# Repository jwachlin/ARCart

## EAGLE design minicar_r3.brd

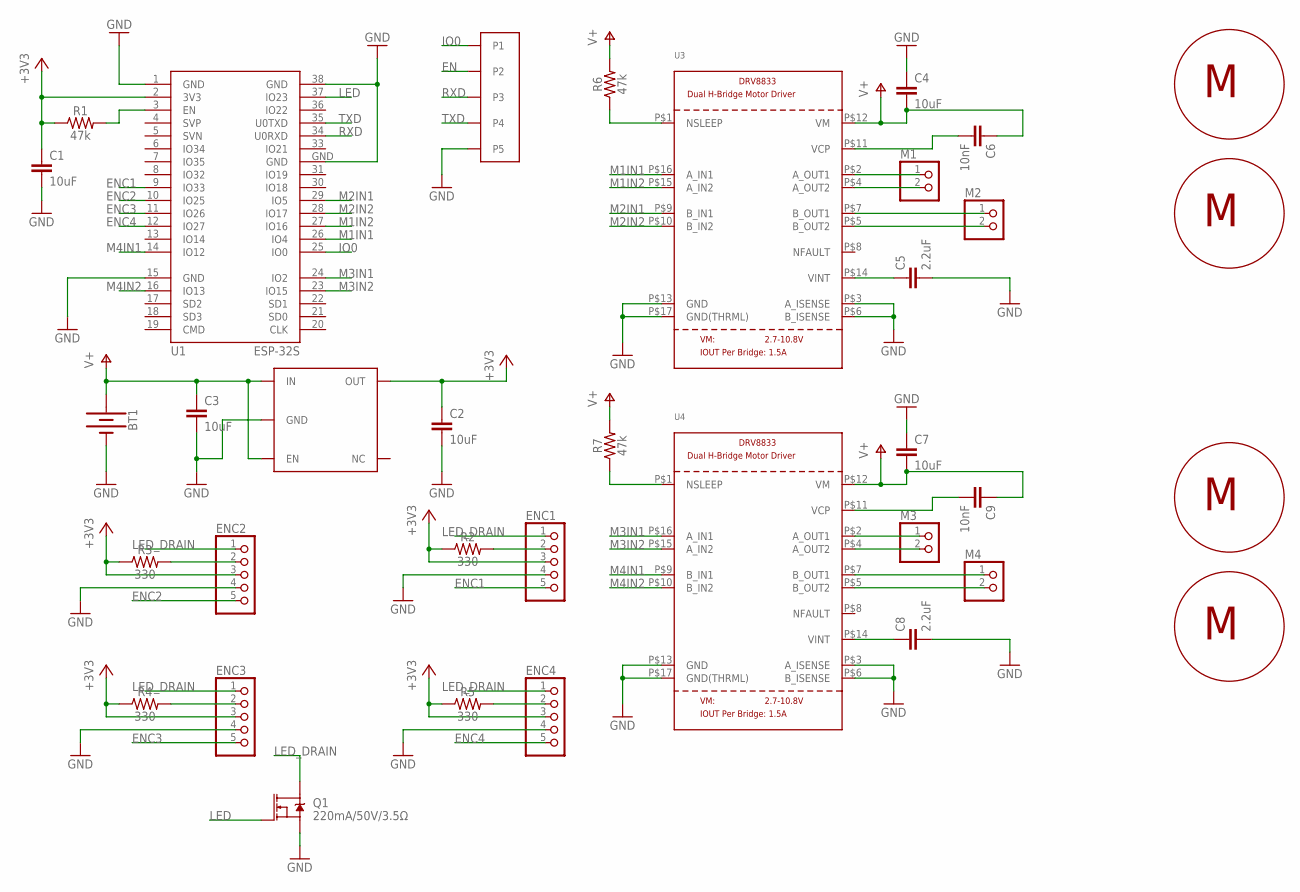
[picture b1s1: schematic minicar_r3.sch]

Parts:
BT1: BATTERY-AA
C1, C2, C3, C4, C7: 10uF; 0805
C5, C8: 2.2uF; 0603
C6, C9: 10nF; 0603
ENC1, ENC2, ENC3, ENC4: PINHD-1X5; 1X05
M1, M2, M3, M4: PINHD-1X2; 1X02
Q1: 220mA/50V/3.5Ω; SOT23-3
R1, R6, R7: 47k; 0603
R2, R3, R4, R5: 330; 0603
U1: ESP-32S
U2: 53047; PICOBLADE_53047
U3, U4: DRV8833; HTSSOP16
U5: TLV755; SOT23-DBV
U$2, U$3, U$4, U$5: MOTOR_10X27MM; MOTOR

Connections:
+3V3: C1.1, C2.1, ENC1.3, ENC2.3, ENC3.3, ENC4.3, R1.1, R2.1, R3.1, R4.1, R5.1, U1.2 (3V3), U5.5 (OUT)
EN: R1.2, U1.3 (EN), U2.P$2 (P2)
ENC1: ENC1.5, U1.9 (IO33)
ENC2: ENC2.5, U1.10 (IO25)
ENC3: ENC3.5, U1.11 (IO26)
ENC4: ENC4.5, U1.12 (IO27)
GND: BT1.GND@1 (-), C1.2, C2.2, C3.2, C4.1, C5.2, C7.1, C8.2, ENC1.4, ENC2.4, ENC3.4, ENC4.4, Q1.2 (S), U1.1 (GND), U1.15 (GND), U1.38 (GND), U1.GND, U2.P$5 (P5), U3.P$3 (A_ISENSE), U3.P$6 (B_ISENSE), U3.P$13 (GND), U3.P$17 (GND(THRML)), U4.P$3 (A_ISENSE), U4.P$6 (B_ISENSE), U4.P$13 (GND), U4.P$17 (GND(THRML)), U5.2 (GND)
IO0: U1.25 (IO0), U2.P$1 (P1)
LED: Q1.1 (G), U1.37 (IO23)
LED_DRAIN: ENC1.1, ENC2.1, ENC3.1, ENC4.1, Q1.3 (D)
M1IN1: U1.26 (IO4), U3.P$16 (A_IN1)
M1IN2: U1.27 (IO16), U3.P$15 (A_IN2)
M2IN1: U1.29 (IO5), U3.P$9 (B_IN1)
M2IN2: U1.28 (IO17), U3.P$10 (B_IN2)
M3IN1: U1.24 (IO2), U4.P$16 (A_IN1)
M3IN2: U1.23 (IO15), U4.P$15 (A_IN2)
M4IN1: U1.14 (IO12), U4.P$9 (B_IN1)
M4IN2: U1.16 (IO13), U4.P$10 (B_IN2)
unnamed: M1.1, U3.P$2 (A_OUT1)
unnamed: M1.2, U3.P$4 (A_OUT2)
unnamed: M2.1, U3.P$7 (B_OUT1)
unnamed: M2.2, U3.P$5 (B_OUT2)
unnamed: C5.1, U3.P$14 (VINT)
unnamed: C6.2, U3.P$11 (VCP)
unnamed: M3.1, U4.P$2 (A_OUT1)
unnamed: M3.2, U4.P$4 (A_OUT2)
unnamed: M4.1, U4.P$7 (B_OUT1)
unnamed: M4.2, U4.P$5 (B_OUT2)
unnamed: C8.1, U4.P$14 (VINT)
unnamed: C9.2, U4.P$11 (VCP)
unnamed: ENC1.2, R2.2
unnamed: ENC4.2, R5.2
unnamed: ENC3.2, R4.2
unnamed: ENC2.2, R3.2
unnamed: R6.1, U3.P$1 (NSLEEP)
unnamed: R7.1, U4.P$1 (NSLEEP)
RXD: U1.34 (U0RXD), U2.P$3 (P3)
TXD: U1.35 (U0TXD), U2.P$4 (P4)
V+: BT1.PWR@1 (+), C3.1, C4.2, C6.1, C7.2, C9.1, R6.2, R7.2, U3.P$12 (VM), U4.P$12 (VM), U5.1 (IN), U5.3 (EN)

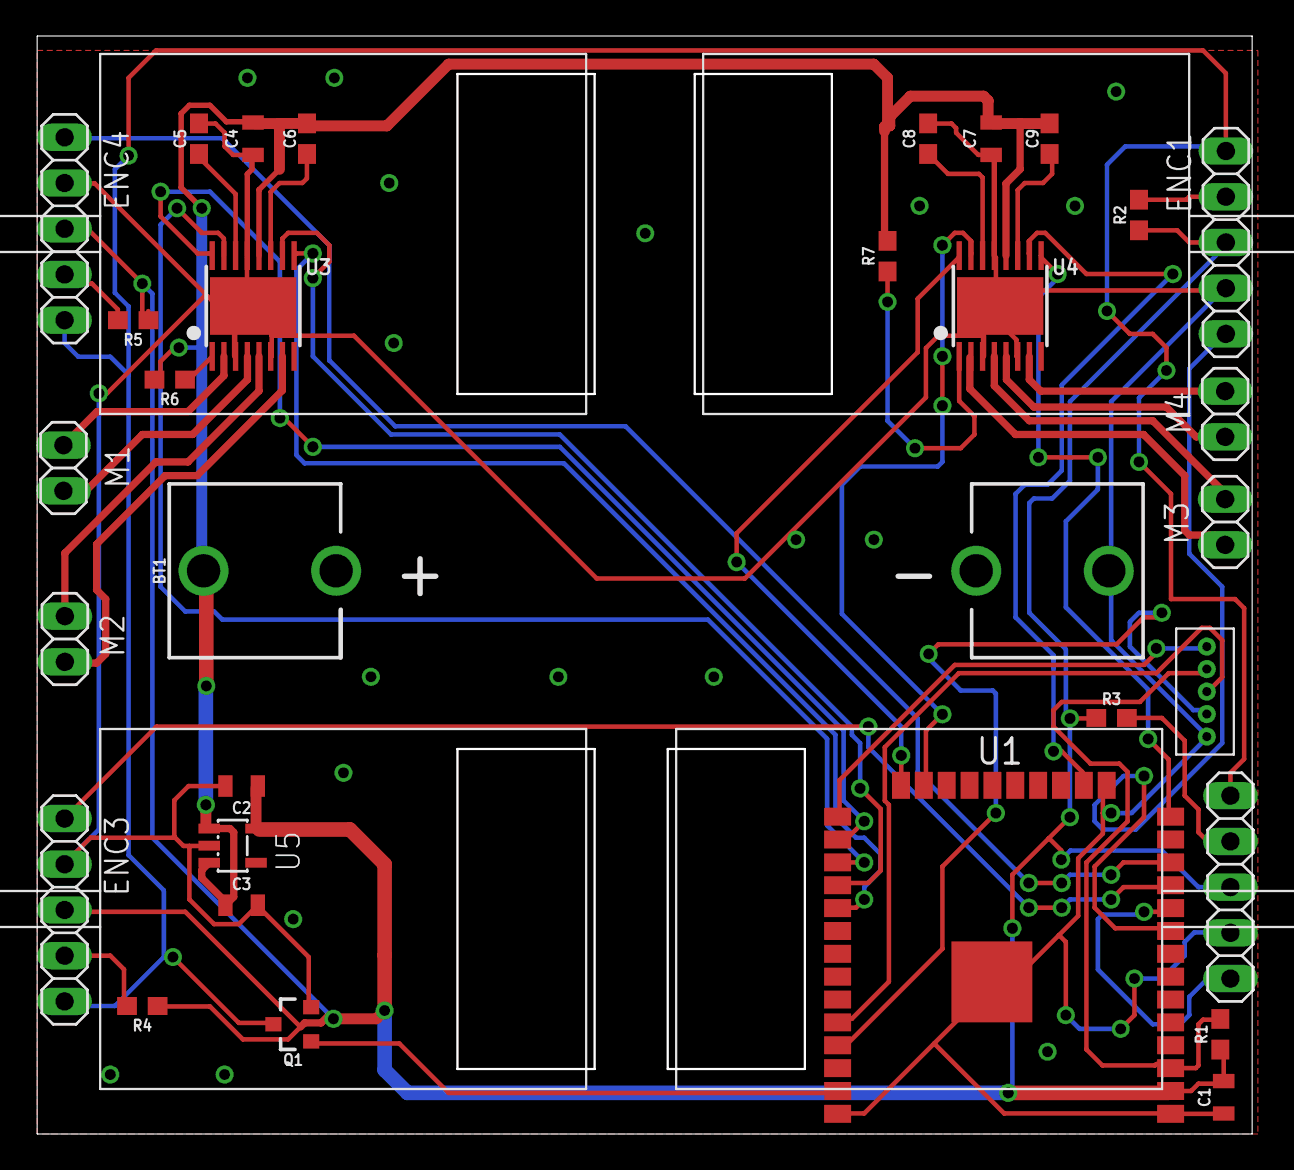
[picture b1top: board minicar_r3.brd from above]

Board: 2 copper layers, 67.4 x 60.9 mm, 35 parts (0 on the bottom side), 39 nets.

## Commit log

2019-04-27 Adds files
2019-04-27 Adds first built prototype PCB files

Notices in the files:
parts and their libraries:
SparkFun-Resistors: Licensing: Creative Commons ShareAlike 4.0 International - https://creativecommons.org/licenses/by-sa/4.0
esp32: Creative Commons Attribution-ShareAlike 4.0 International
